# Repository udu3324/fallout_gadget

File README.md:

# fallout gadget

this is a fallout gadget

it is a pager/fun display, and is an ap device that people can connect and interact with nearby

# bom

 * PCB (no pcba) and stencil
 * 36x SK6812 Neopixels
 * 2x 6mm Tactile Buttons
 * 1x EC11 Rotary Encoder
 * 1x Seeed Xiao ESP32-C3

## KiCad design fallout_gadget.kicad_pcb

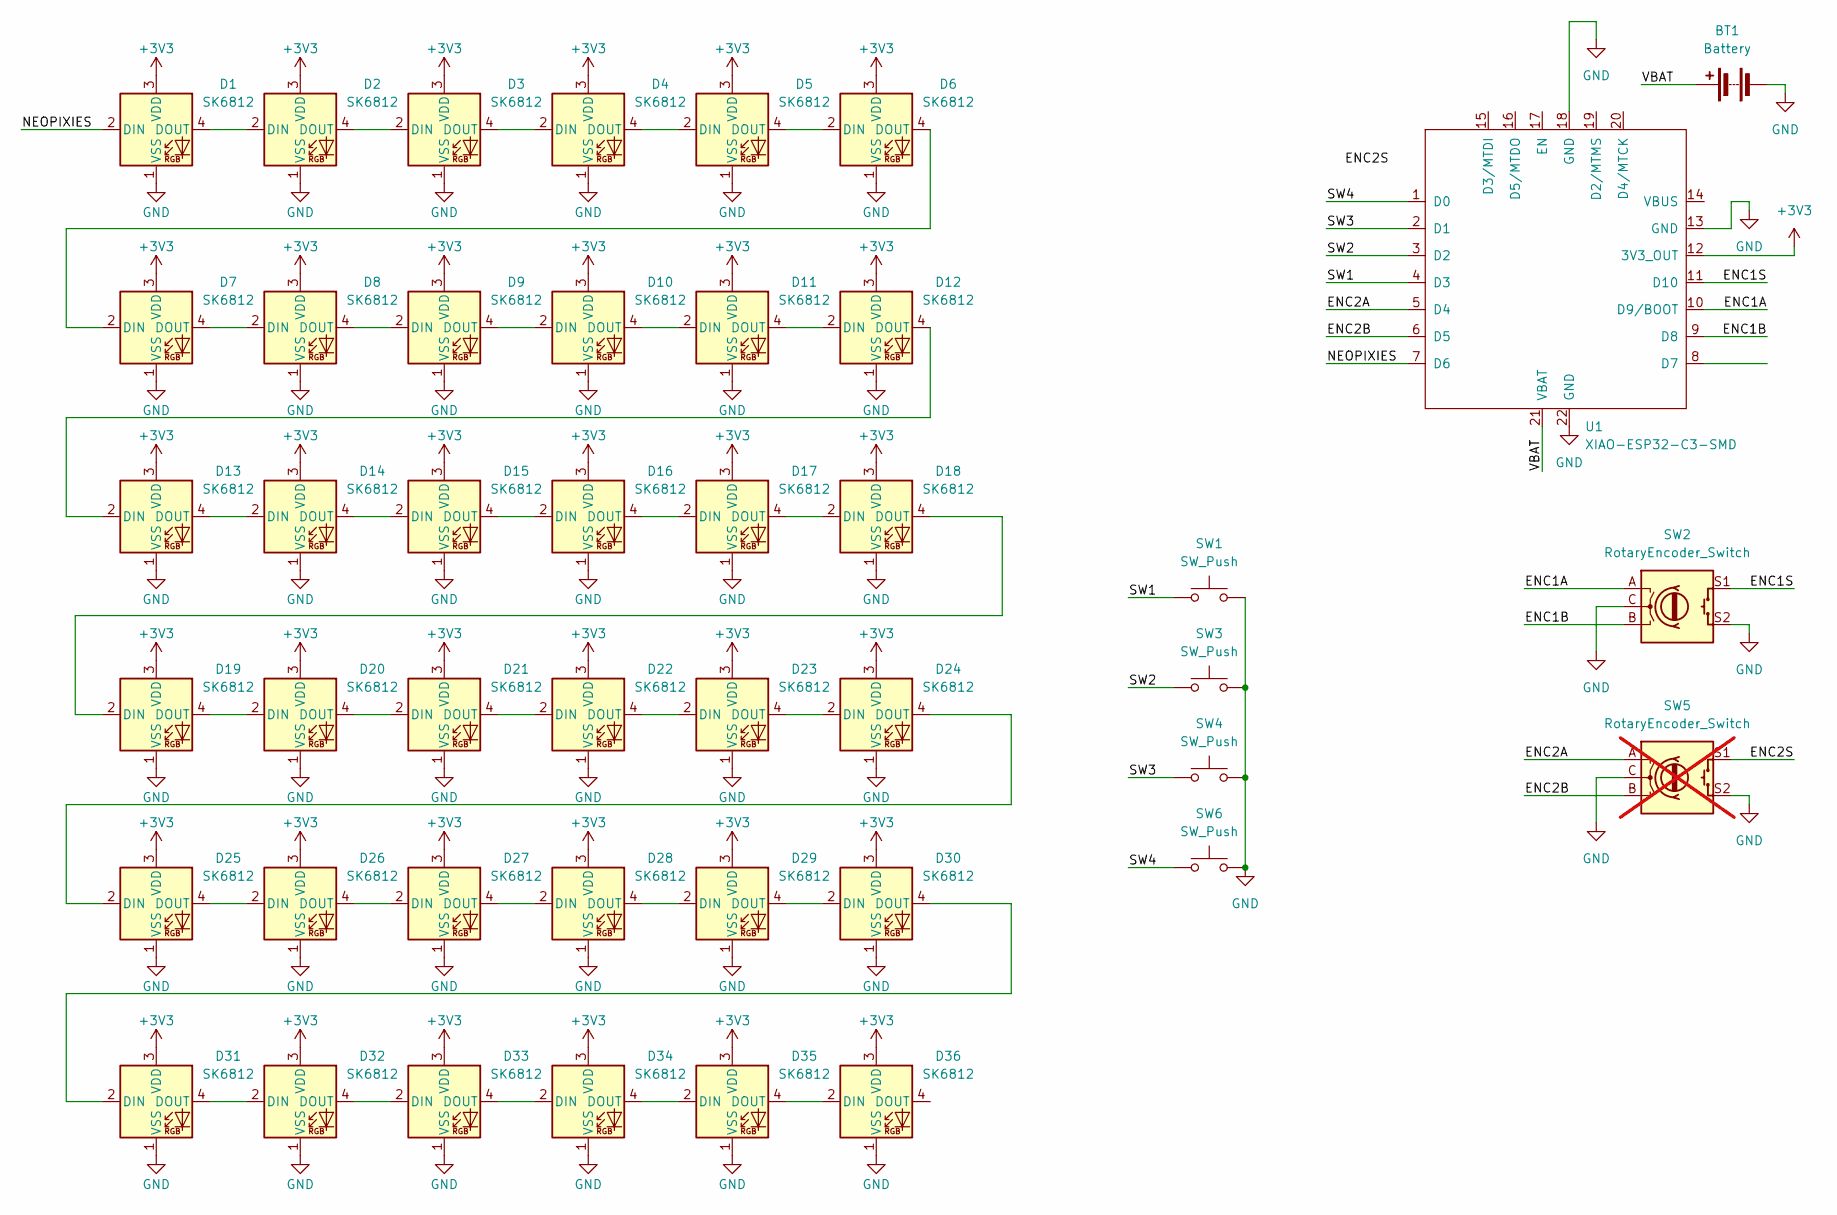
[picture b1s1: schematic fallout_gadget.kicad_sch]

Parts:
BT1: Battery; SolderWire-0.15sqmm_1x02_P4mm_D0.5mm_OD1.5mm
D1, D2, D3, D4, D5, D6, D7, D8, D9, D10, D11, D12, D13, D14, D15, D16, D17, D18, D19, D20, D21, D22, D23, D24, D25, D26, D27, D28, D29, D30, D31, D32, D33, D34, D35, D36: SK6812; LED_SK6812_PLCC4_5.0x5.0mm_P3.2mm
SW1, SW3, SW4, SW6: SW_Push; SW_PUSH_6mm
SW2: RotaryEncoder_Switch; RotaryEncoder_Alps_EC11E-Switch_Vertical_H20mm
SW5: RotaryEncoder_Switch; RotaryEncoder_Alps_EC11E-Switch_Vertical_H20mm; not fitted
U1: XIAO-ESP32-C3-SMD

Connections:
+3V3: D1.3 (VDD), D2.3 (VDD), D3.3 (VDD), D4.3 (VDD), D5.3 (VDD), D6.3 (VDD), D7.3 (VDD), D8.3 (VDD), D9.3 (VDD), D10.3 (VDD), D11.3 (VDD), D12.3 (VDD), D13.3 (VDD), D14.3 (VDD), D15.3 (VDD), D16.3 (VDD), D17.3 (VDD), D18.3 (VDD), D19.3 (VDD), D20.3 (VDD), D21.3 (VDD), D22.3 (VDD), D23.3 (VDD), D24.3 (VDD), D25.3 (VDD), D26.3 (VDD), D27.3 (VDD), D28.3 (VDD), D29.3 (VDD), D30.3 (VDD), D31.3 (VDD), D32.3 (VDD), D33.3 (VDD), D34.3 (VDD), D35.3 (VDD), D36.3 (VDD), U1.12 (3V3_OUT)
/ENC1A: SW2.A, U1.10 (D9/BOOT)
/ENC1B: SW2.B, U1.9 (D8)
/ENC1S: SW2.S1, U1.11 (D10)
/ENC2A: SW5.A, U1.5 (D4)
/ENC2B: SW5.B, U1.6 (D5)
/NEOPIXIES: D1.2 (DIN), U1.7 (D6)
/SW1: SW1.1, U1.4 (D3)
/SW2: SW3.1, U1.3 (D2)
/SW3: SW4.1, U1.2 (D1)
/SW4: SW6.1, U1.1 (D0)
/VBAT: BT1.1 (+), U1.21 (VBAT)
GND: BT1.2 (-), D1.1 (VSS), D2.1 (VSS), D3.1 (VSS), D4.1 (VSS), D5.1 (VSS), D6.1 (VSS), D7.1 (VSS), D8.1 (VSS), D9.1 (VSS), D10.1 (VSS), D11.1 (VSS), D12.1 (VSS), D13.1 (VSS), D14.1 (VSS), D15.1 (VSS), D16.1 (VSS), D17.1 (VSS), D18.1 (VSS), D19.1 (VSS), D20.1 (VSS), D21.1 (VSS), D22.1 (VSS), D23.1 (VSS), D24.1 (VSS), D25.1 (VSS), D26.1 (VSS), D27.1 (VSS), D28.1 (VSS), D29.1 (VSS), D30.1 (VSS), D31.1 (VSS), D32.1 (VSS), D33.1 (VSS), D34.1 (VSS), D35.1 (VSS), D36.1 (VSS), SW1.2, SW2.C, SW2.S2, SW3.2, SW4.2, SW5.C, SW5.S2, SW6.2, U1.13 (GND), U1.18 (GND), U1.22 (GND)
unnamed: D1.4 (DOUT), D2.2 (DIN)
unnamed: D2.4 (DOUT), D3.2 (DIN)
unnamed: D3.4 (DOUT), D4.2 (DIN)
unnamed: D4.4 (DOUT), D5.2 (DIN)
unnamed: D5.4 (DOUT), D6.2 (DIN)
unnamed: D6.4 (DOUT), D7.2 (DIN)
unnamed: D7.4 (DOUT), D8.2 (DIN)
unnamed: D8.4 (DOUT), D9.2 (DIN)
unnamed: D9.4 (DOUT), D10.2 (DIN)
unnamed: D10.4 (DOUT), D11.2 (DIN)
unnamed: D11.4 (DOUT), D12.2 (DIN)
unnamed: D12.4 (DOUT), D13.2 (DIN)
unnamed: D13.4 (DOUT), D14.2 (DIN)
unnamed: D14.4 (DOUT), D15.2 (DIN)
unnamed: D15.4 (DOUT), D16.2 (DIN)
unnamed: D16.4 (DOUT), D17.2 (DIN)
unnamed: D17.4 (DOUT), D18.2 (DIN)
unnamed: D18.4 (DOUT), D19.2 (DIN)
unnamed: D19.4 (DOUT), D20.2 (DIN)
unnamed: D20.4 (DOUT), D21.2 (DIN)
unnamed: D21.4 (DOUT), D22.2 (DIN)
unnamed: D22.4 (DOUT), D23.2 (DIN)
unnamed: D23.4 (DOUT), D24.2 (DIN)
unnamed: D24.4 (DOUT), D25.2 (DIN)
unnamed: D25.4 (DOUT), D26.2 (DIN)
unnamed: D26.4 (DOUT), D27.2 (DIN)
unnamed: D27.4 (DOUT), D28.2 (DIN)
unnamed: D28.4 (DOUT), D29.2 (DIN)
unnamed: D29.4 (DOUT), D30.2 (DIN)
unnamed: D30.4 (DOUT), D31.2 (DIN)
unnamed: D31.4 (DOUT), D32.2 (DIN)
unnamed: D32.4 (DOUT), D33.2 (DIN)
unnamed: D33.4 (DOUT), D34.2 (DIN)
unnamed: D34.4 (DOUT), D35.2 (DIN)
unnamed: D35.4 (DOUT), D36.2 (DIN)

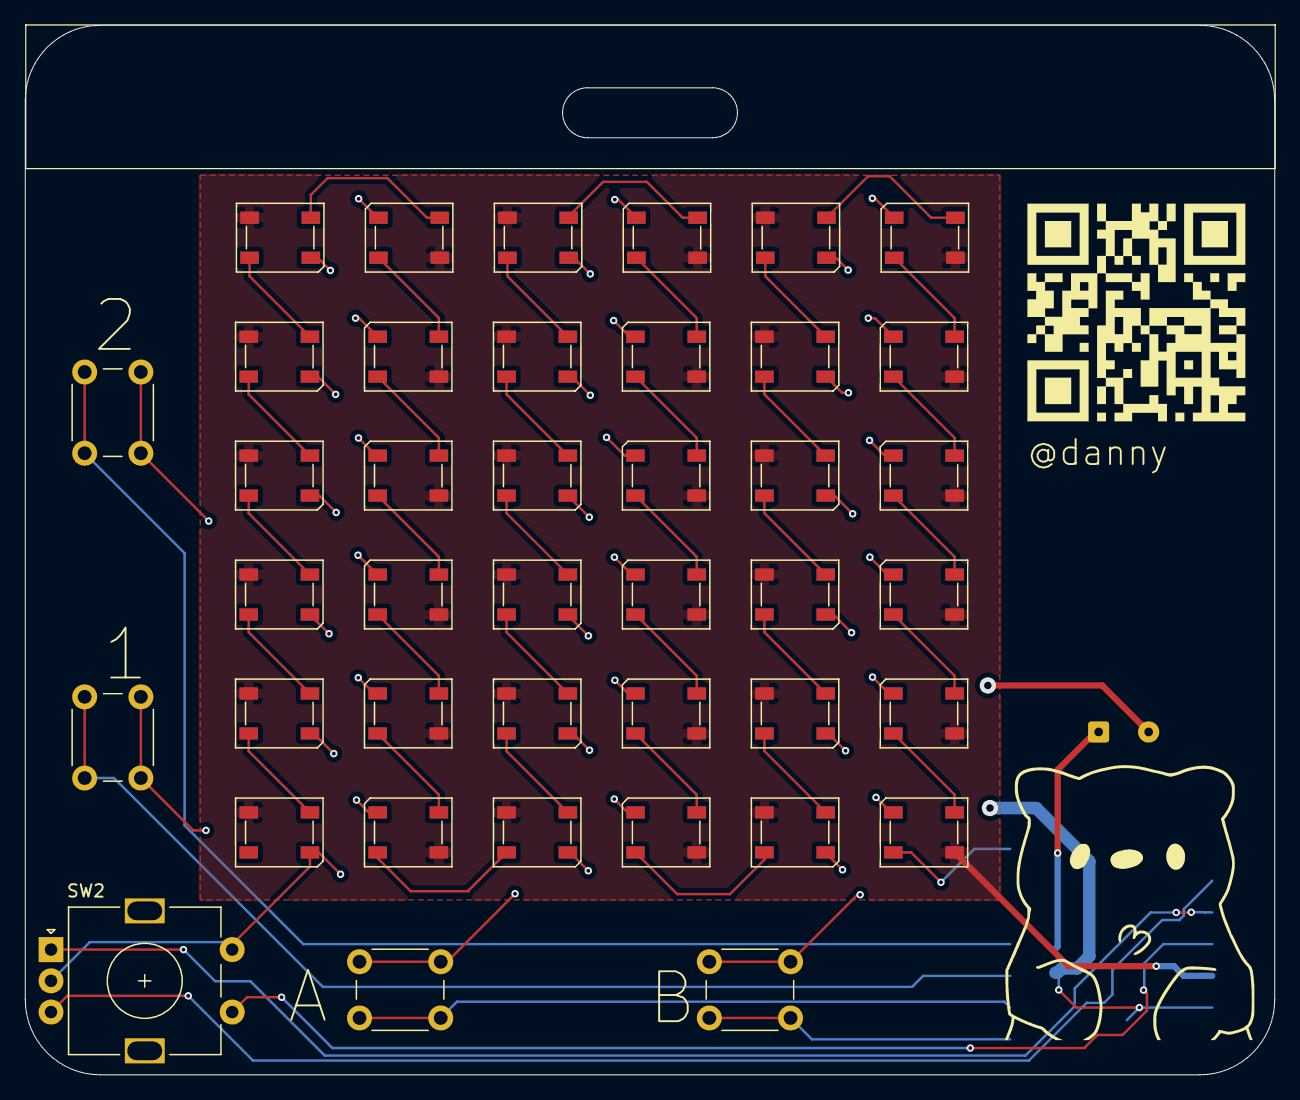
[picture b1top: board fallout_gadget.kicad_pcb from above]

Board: 2 copper layers, 100.0 x 84.0 mm, 43 parts (1 on the bottom side), 46 nets.

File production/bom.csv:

Designator,Footprint,Quantity,Value,LCSC Part #
BT1,SolderWire-0.15sqmm_1x02_P4mm_D0.5mm_OD1.5mm,1,Battery,
"D1, D10, D11, D12, D13, D14, D15, D16, D17, D18, D19, D2, D20, D21, D22, D23, D24, D25, D26, D27, D28, D29, D3, D30, D31, D32, D33, D34, D35, D36, D4, D5, D6, D7, D8, D9",LED_SK6812_PLCC4_5.0x5.0mm_P3.2mm,36,SK6812,
"SW1, SW3, SW4, SW6",SW_PUSH_6mm,4,SW_Push,
SW2,RotaryEncoder_Alps_EC11E-Switch_Vertical_H20mm,1,RotaryEncoder_Switch,
U1,XIAO-ESP32-C3-SMD,1,XIAO-ESP32-C3-SMD,
